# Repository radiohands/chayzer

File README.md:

# chayzer
Go in to the individual directories for more information

### Chayzer Chording keyboard

Board that I designed to be used with the https://artsey.io chording layout. Of course this can be modified to work in other ways "macro pad" etc.

When using an OLED screen on the pcb, make sure the pin's match, there are some versions that you can buy that have the wrong pin locations for this board

If you use the latter, you will have to somehow twist the pins around without having them touch... (not easy and can dammage it)
```
Supposed to be (looking from the top):
GND VCC SCL SDA

NOT:
VCC GND SCL SDA
```
---

---

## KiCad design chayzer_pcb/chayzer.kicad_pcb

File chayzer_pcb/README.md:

# chayzer_pcb

PCB design for chayzer

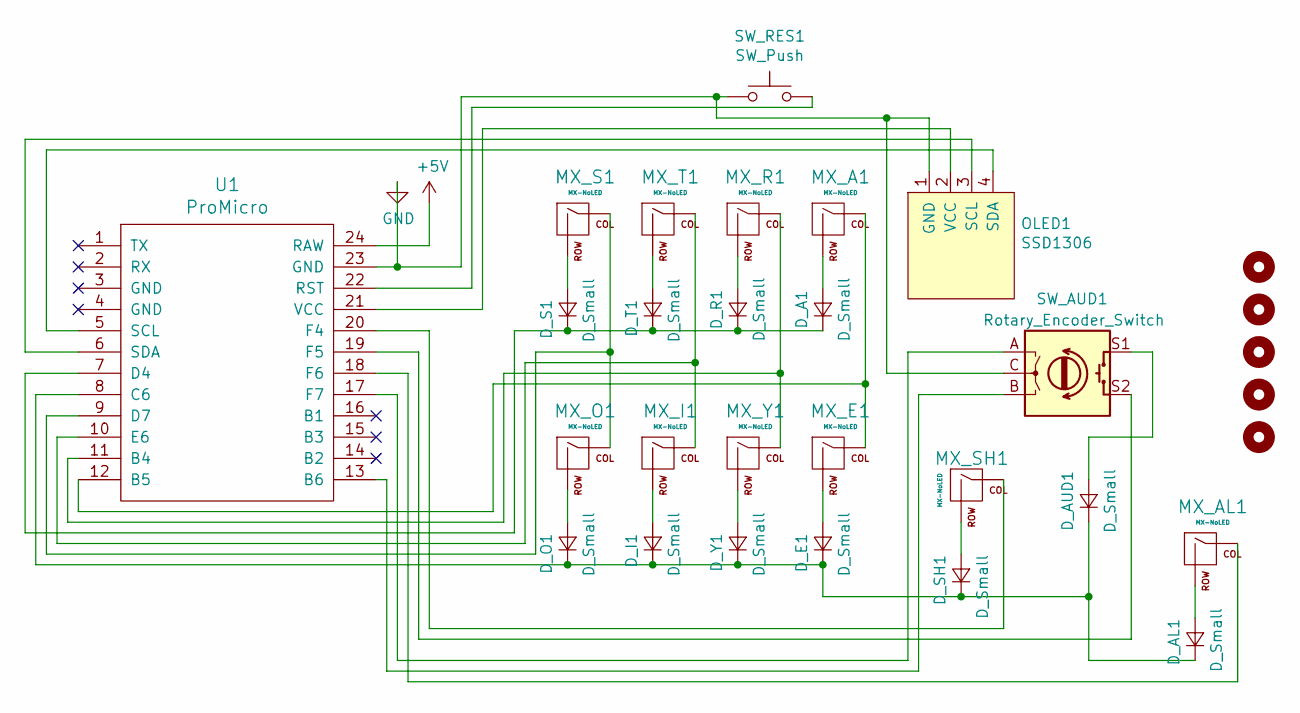
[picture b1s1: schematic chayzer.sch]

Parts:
D_A1: D_Small; D_DO-35_SOD27_P7.62mm_Horizontal
D_AL1: D_Small; D_DO-35_SOD27_P7.62mm_Horizontal
D_AUD1: D_Small; D_DO-35_SOD27_P7.62mm_Horizontal
D_E1: D_Small; D_DO-35_SOD27_P7.62mm_Horizontal
D_I1: D_Small; D_DO-35_SOD27_P7.62mm_Horizontal
D_O1: D_Small; D_DO-35_SOD27_P7.62mm_Horizontal
D_R1: D_Small; D_DO-35_SOD27_P7.62mm_Horizontal
D_S1: D_Small; D_DO-35_SOD27_P7.62mm_Horizontal
D_SH1: D_Small; D_DO-35_SOD27_P7.62mm_Horizontal
D_T1: D_Small; D_DO-35_SOD27_P7.62mm_Horizontal
D_Y1: D_Small; D_DO-35_SOD27_P7.62mm_Horizontal
H1, H2, H3, H4, H5: MountingHole; MountingHole_3.2mm_M3
MX_A1: MX-NoLED; Kailh_socket_MX_optional
MX_AL1: MX-NoLED; Kailh_socket_MX_optional
MX_E1: MX-NoLED; Kailh_socket_MX_optional
MX_I1: MX-NoLED; Kailh_socket_MX_optional
MX_O1: MX-NoLED; Kailh_socket_MX_optional
MX_R1: MX-NoLED; Kailh_socket_MX_optional
MX_S1: MX-NoLED; Kailh_socket_MX_optional
MX_SH1: MX-NoLED; Kailh_socket_MX_optional
MX_T1: MX-NoLED; Kailh_socket_MX_optional
MX_Y1: MX-NoLED; Kailh_socket_MX_optional
OLED1: SSD1306; 128x64OLED
SW_AUD1: Rotary_Encoder_Switch; RotaryEncoder_Alps_EC12E-Switch_Vertical_H20mm
SW_RES1: SW_Push; SW_PUSH_6mm_H4.3mm
U1: ProMicro

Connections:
5v: U1.24 (RAW); also elsewhere on the board
B1: U1.16 (B1); also elsewhere on the board
B4: MX_R1.1 (COL), MX_Y1.1 (COL), U1.11 (B4)
B5: MX_A1.1 (COL), MX_E1.1 (COL), U1.12 (B5)
B6: SW_AUD1.B, U1.13 (B6)
C6: D_AL1.1 (K), D_AUD1.1 (K), D_E1.1 (K), D_I1.1 (K), D_O1.1 (K), D_SH1.1 (K), D_Y1.1 (K), U1.8 (C6)
D4: D_A1.1 (K), D_R1.1 (K), D_S1.1 (K), D_T1.1 (K), U1.7 (D4)
D7: MX_O1.1 (COL), MX_S1.1 (COL), U1.9 (D7)
E6: MX_I1.1 (COL), MX_T1.1 (COL), U1.10 (E6)
F4: MX_SH1.1 (COL), U1.20 (F4)
F5: SW_AUD1.S2, U1.19 (F5)
F6: MX_AL1.1 (COL), U1.18 (F6)
F7: SW_AUD1.A, U1.17 (F7)
GND: OLED1.1 (GND), SW_AUD1.C, SW_RES1.1, U1.23 (GND); also elsewhere on the board
unnamed: D_A1.2 (A), MX_A1.2 (ROW)
unnamed: D_AL1.2 (A), MX_AL1.2 (ROW)
unnamed: D_AUD1.2 (A), SW_AUD1.S1
unnamed: D_E1.2 (A), MX_E1.2 (ROW)
unnamed: D_I1.2 (A), MX_I1.2 (ROW)
unnamed: D_O1.2 (A), MX_O1.2 (ROW)
unnamed: D_R1.2 (A), MX_R1.2 (ROW)
unnamed: D_S1.2 (A), MX_S1.2 (ROW)
unnamed: D_SH1.2 (A), MX_SH1.2 (ROW)
unnamed: D_T1.2 (A), MX_T1.2 (ROW)
unnamed: D_Y1.2 (A), MX_Y1.2 (ROW)
RST: SW_RES1.2, U1.22 (RST)
SCL: OLED1.3 (SCL), U1.6 (SDA)
SDA: OLED1.4 (SDA), U1.5 (SCL)
VCC: OLED1.2 (VCC), U1.21 (VCC)

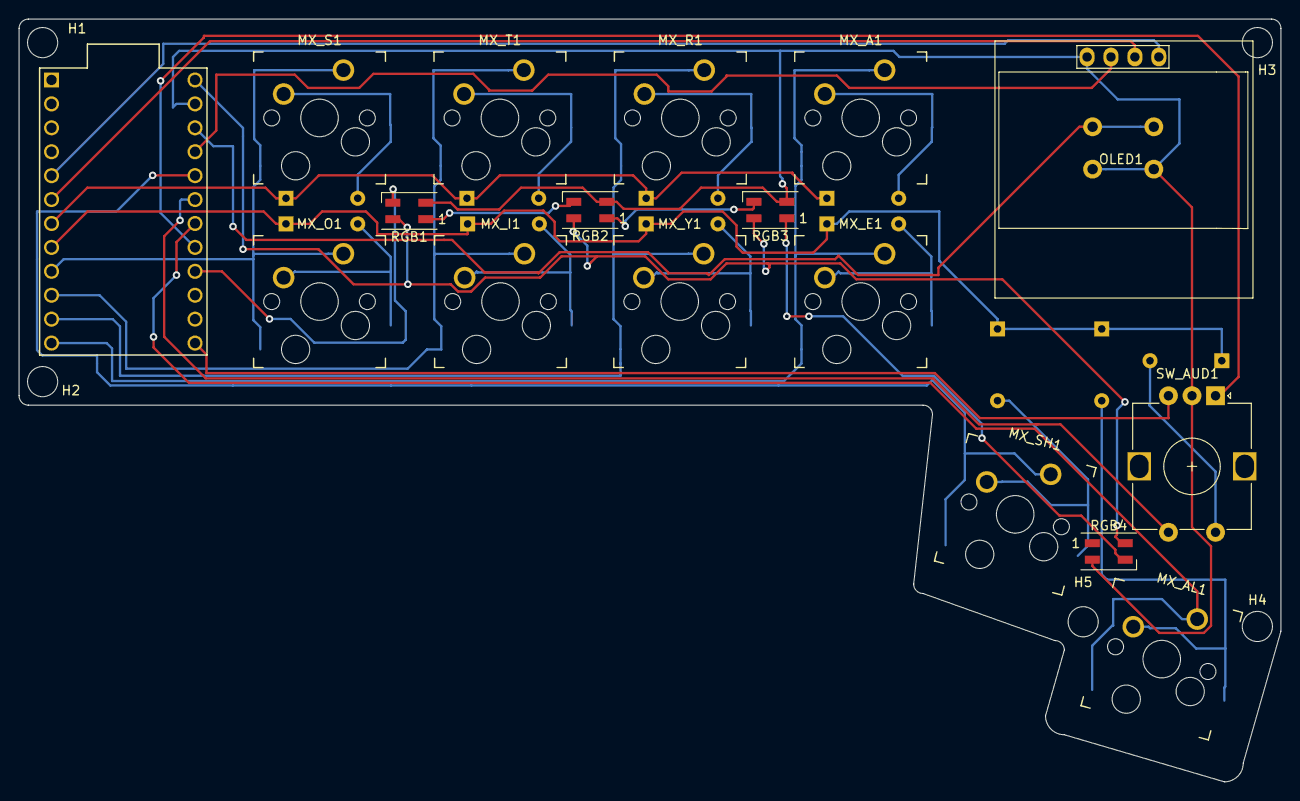
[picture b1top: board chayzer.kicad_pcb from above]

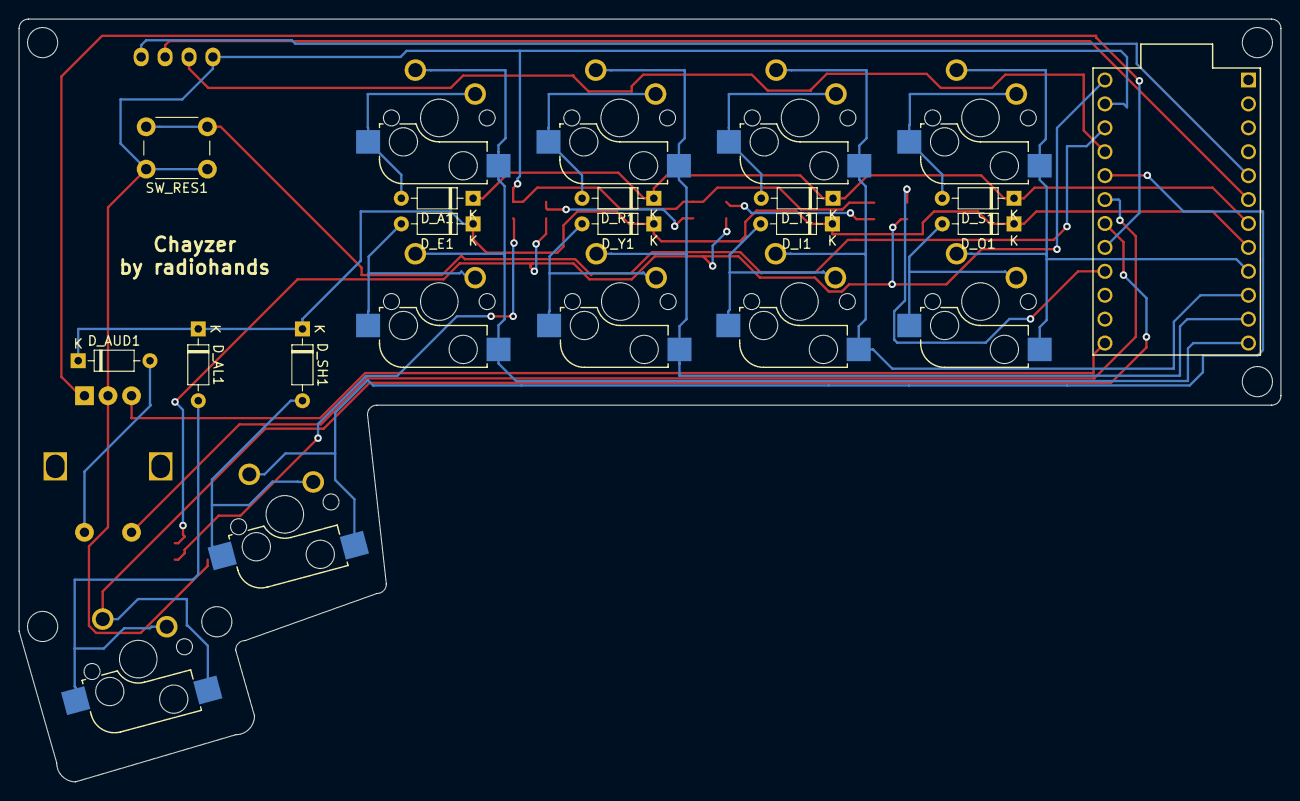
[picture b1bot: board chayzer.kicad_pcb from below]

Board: 2 copper layers, 134.0 x 81.0 mm, 34 parts (12 on the bottom side), 32 nets.

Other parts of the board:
RGB1, RGB2, RGB3, RGB4: SK6812MINI; LED_SK6812MINI_PLCC4_3.5x3.5mm_P1.75mm

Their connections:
5v: RGB1.4, RGB2.4, RGB3.4, RGB4.4; also elsewhere on the board
B1: RGB1.3; also elsewhere on the board
GND: RGB1.2, RGB2.2, RGB3.2, RGB4.2; also elsewhere on the board
unnamed: RGB1.1, RGB2.3
unnamed: RGB2.1, RGB3.3
unnamed: RGB3.1, RGB4.3

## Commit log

2021-07-25 initial file upload
2021-07-27 cleared up the readme a little
2021-07-27 moved the encoder up a bit
2021-07-27 cleaned up schematic
2021-07-31 added rgb to PCB, buggy in qmk right now, and untested on PCB
